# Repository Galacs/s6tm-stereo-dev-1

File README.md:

# S6TM Stereo Dev 1

ESP32S3 based stereo audio developement board with oled display

## IC List

- ESP32-S3FH4R2 (Main MCU)
- x4 LDL212 (LDOs)
- LM74502H (RPP, OCP)
- TPS629330 (5V out of audio SMPS)
- TLV320AIC (CODEC)
- TPA3116D2 (2x 30W audio amplifier)
- TPA3116D2 (OLED display)

## Top preview

## Preview 3d render

## Pictures

## Pin definitions

```c
#define SD_DAT0_PIN 33
#define SD_DAT1_PIN 47
#define SD_DAT2_PIN 37
#define SD_DAT3_PIN 36
#define SD_CLK_PIN 34
#define SD_CMD_PIN 35

#define SW_A_PIN 2
#define BTN_A_PIN 4
#define BTN_B_PIN 3

#define PG_PIN 5
#define VSNS_PIN 6

#define I2C_SDA_PIN 8
#define I2C_SCL_PIN 7

#define ENC_A_PIN 38
#define ENC_B_PIN 39
#define ENC_SW 40

#define FAULTZ_PIN 17
#define MUTE_PIN 21

#define GPIO1_PIN 15
#define RESET_PIN 16
#define BCLK_PIN 10
#define DOUT_PIN 13
#define DIN_PIN 12
#define MCLK_PIN 9
#define WCLK_PIN 11
```

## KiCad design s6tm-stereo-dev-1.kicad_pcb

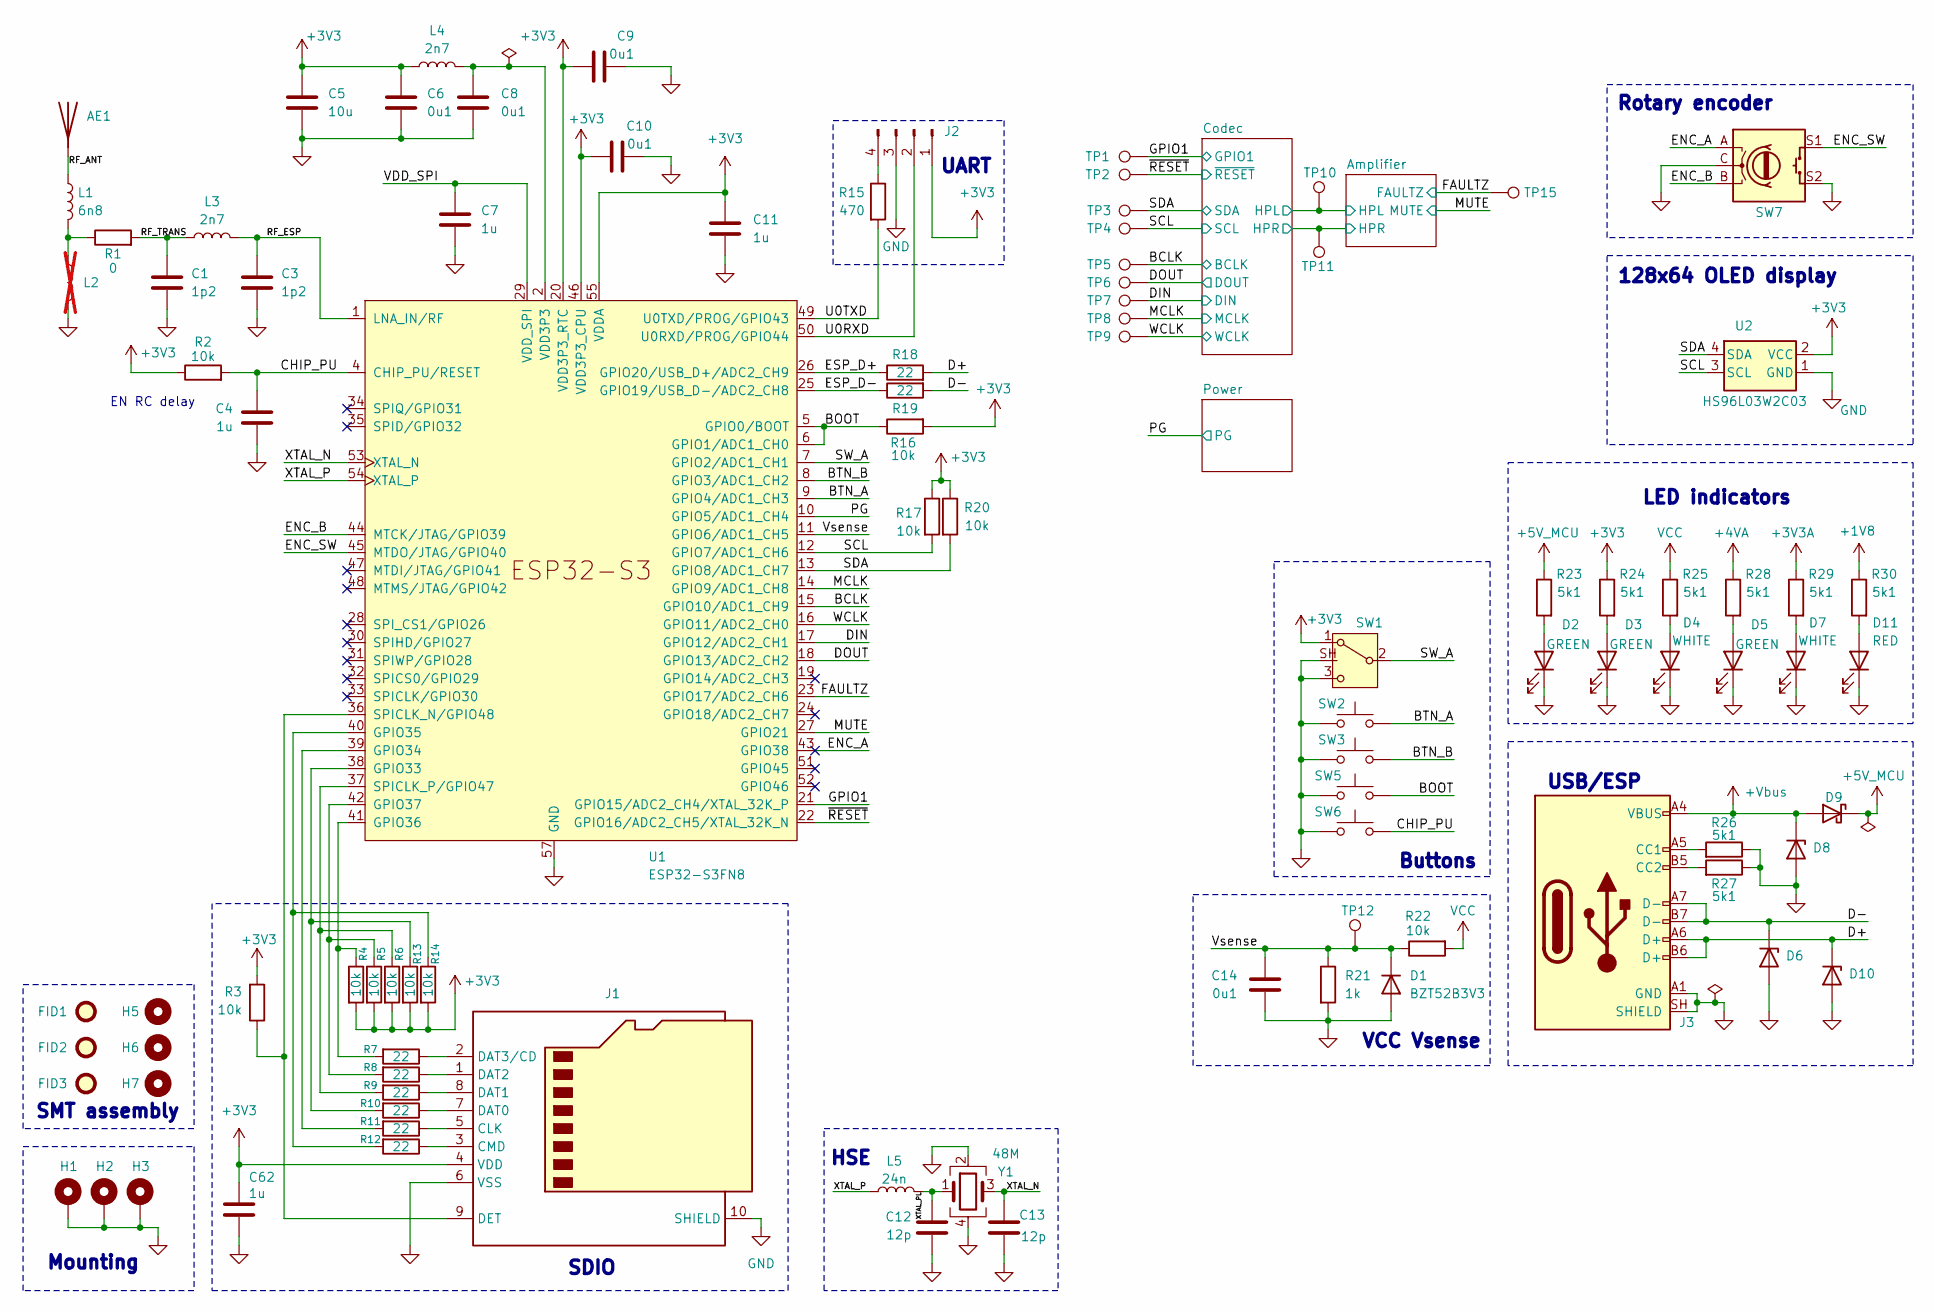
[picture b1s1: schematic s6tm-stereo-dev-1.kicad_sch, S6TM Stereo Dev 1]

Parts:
AE1: Antenna; Johanson_2450AT18x100; Manufacturer Part Number RFANT3216120A5T; JLCPCB Part # C127629
C1, C3: 1p2; C_0402_1005Metric; Manufacturer Part Number GJM1555C1H1R2WB01D; JLCPCB Part # C76899
C4, C7, C11, C62: 1u; C_0402_1005Metric; Manufacturer Part Number CL05A105KA5NQNC; JLCPCB Part # C52923
C5: 10u; C_0402_1005Metric; Manufacturer Part Number CL05A106MQ5NUNC; JLCPCB Part # C15525
C6, C8, C9, C10, C14: 0u1; C_0402_1005Metric; Manufacturer Part Number CL05B104KB54PNC; JLCPCB Part # C307331
C12, C13: 12p; C_0402_1005Metric; Manufacturer Part Number 0402CG120J500NT; JLCPCB Part # C1547
D1: BZT52B3V3; D_SOD-123; Manufacturer Part Number BZT52B3V3; JLCPCB Part # C19077392
D2, D3, D5: GREEN; LED_0805_2012Metric; Manufacturer Part Number KT-0805G; JLCPCB Part # C2297
D4, D7: WHITE; LED_0603_1608Metric; Manufacturer Part Number KT-0603W; JLCPCB Part # C2290
D6, D8, D10: H5VU10U; Diode_DFN1006; Manufacturer Part Number H5VU10U; JLCPCB Part # C22395519
D9: D_Schottky; D_SMA; Manufacturer Part Number SS54; JLCPCB Part # C22452
D11: RED; LED_0805_2012Metric; Manufacturer Part Number NCD0805R1; JLCPCB Part # NCD0805R1
FID1, FID2, FID3: Fiducial; Fiducial_1mm_Mask2mm
H1, H2, H3: MountingHole_Pad; MountingHole_3.2mm_M3_Pad_Via
H5, H6, H7: MountingHole; ToolingHole_1.152mm
J1: Micro_SD_Card_Det1; microSD_Hanbo_TF012; Manufacturer Part Number TF-012; JLCPCB Part # C410350
J2: Conn_01x04_Pin; PinHeader_1x04_P2.54mm_Vertical
J3: USB_C_Receptacle_USB2.0_14P; USB_C_Receptacle_HRO_TYPE-C-31-M-12; Manufacturer Part Number TYPE-C16PIN; JLCPCB Part # C393939
L1: 6n8; L_0402_1005Metric; Manufacturer Part Number LQG15HS6N8J02D; JLCPCB Part # C77110
L2: L; L_0402_1005Metric; not fitted
L3, L4: 2n7; L_0402_1005Metric; Manufacturer Part Number LQG15HS2N7S02D; JLCPCB Part # C77108
L5: 24n; L_0402_1005Metric; Manufacturer Part Number LQW15AN24NG00D; JLCPCB Part # C167472
R1: 0; R_0402_1005Metric; Manufacturer Part Number 0402WGF0000TCE; JLCPCB Part # C17168
R2, R3, R4, R5, R6, R13, R14, R16, R17, R20, R22: 10k; R_0402_1005Metric; Manufacturer Part Number 0402WGF1002TCE; JLCPCB Part # C25744
R7, R8, R9, R10, R11, R12, R18, R19: 22; R_0402_1005Metric; Manufacturer Part Number 0402WGF220JTCE; JLCPCB Part # C25092
R15: 470; R_0402_1005Metric; Manufacturer Part Number 0402WGF4700TCE; JLCPCB Part # C25117
R21: 1k; R_0402_1005Metric; Manufacturer Part Number 0402WGF1001TCE; JLCPCB Part # C11702
R23, R24, R25, R26, R27, R28, R29, R30: 5k1; R_0402_1005Metric; Manufacturer Part Number 0402WGF5101TCE; JLCPCB Part # C25905
SW1: SW_SPDT; SW_SPDT_Shouhan_MSK12C02; Manufacturer Part Number MSK12C02; JLCPCB Part # C431540
SW2, SW3: SW_Push; SW_SPST_Omron_B3F-40xx; Manufacturer Part Number B3F-4055; JLCPCB Part # C84931
SW5, SW6: SW_Push; SW_SPST_TS-1088-xR020; Manufacturer Part Number TS-1088-AR02016; JLCPCB Part # C720477
SW7: RotaryEncoder_Switch; RotaryEncoder_Alps_EC11E-Switch_Vertical_H20mm; Manufacturer Part Number EC11E15244G1; JLCPCB Part # C370970
TP1, TP2, TP12, TP15: TestPoint; TestPoint_Pad_D2.0mm
TP3, TP4, TP5, TP6, TP7, TP8, TP9, TP10, TP11: TestPoint; TestPoint_Keystone_5015_Micro_Mini; Manufacturer Part Number 5015; JLCPCB Part # C2906768
U1: ESP32-S3FN8; QFN-56-1EP_7x7mm_P0.4mm_EP4x4mm_ThermalVias; Manufacturer Part Number ESP32-S3FH4R2; JLCPCB Part # C3013940
U2: HS96L03W2C03
Y1: 48M; Crystal_SMD_2016-4Pin_2.0x1.6mm; Manufacturer Part Number R940000096; JLCPCB Part # C7206306

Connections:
+1V8: R30.1; also elsewhere on the board
+3V3: C5.1, C6.1, C9.1, C10.1, C11.1, C62.1, J1.4 (VDD), J2.1, L4.1, R2.1, R3.2, R4.2, R5.2, R6.2, R13.2, R14.2, R16.2, R17.1, R20.1, R24.1, SW1.1 (A), U1.20 (VDD3P3_RTC), U1.46 (VDD3P3_CPU), U1.55 (VDDA), U1.56 (VDDA), U2.2 (VCC); also elsewhere on the board
+3V3A: R29.1; also elsewhere on the board
+4VA: R28.1; also elsewhere on the board
+5V_MCU: D9.1 (K), R23.1; also elsewhere on the board
+Vbus: D8.1 (K), D9.2 (A), J3.A4 (VBUS), J3.A9 (VBUS), J3.B4 (VBUS), J3.B9 (VBUS)
/Amplifier/HPL: TP10.1 (1_1); also elsewhere on the board
/Amplifier/HPR: TP11.1 (1_1); also elsewhere on the board
/BCLK: TP5.1 (1_1), U1.15 (GPIO10/ADC1_CH9); also elsewhere on the board
/BOOT: R16.1, SW5.2, U1.5 (GPIO0/BOOT), U1.6 (GPIO1/ADC1_CH0)
/BTN_A: SW2.1, U1.9 (GPIO4/ADC1_CH3)
/BTN_B: SW3.1, U1.8 (GPIO3/ADC1_CH2)
/CHIP_PU: C4.1, R2.2, SW6.2, U1.4 (CHIP_PU/RESET)
/D+: D10.1 (K), J3.A6 (D+), J3.B6 (D+), R18.2
/D-: D6.1 (K), J3.A7 (D-), J3.B7 (D-), R19.2
/DIN: TP7.1 (1_1), U1.17 (GPIO12/ADC2_CH1); also elsewhere on the board
/DOUT: TP6.1 (1_1), U1.18 (GPIO13/ADC2_CH2); also elsewhere on the board
/ENC_A: SW7.A, U1.43 (GPIO38)
/ENC_B: SW7.B, U1.44 (MTCK/JTAG/GPIO39)
/ENC_SW: SW7.S1, U1.45 (MTDO/JTAG/GPIO40)
/ESP_D+: R18.1, U1.26 (GPIO20/USB_D+/ADC2_CH9)
/ESP_D-: R19.1, U1.25 (GPIO19/USB_D-/ADC2_CH8)
/FAULTZ: TP15.1 (1_1), U1.23 (GPIO17/ADC2_CH6); also elsewhere on the board
/GPIO1: TP1.1 (1_1), U1.21 (GPIO15/ADC2_CH4/XTAL_32K_P); also elsewhere on the board
/MCLK: TP8.1 (1_1), U1.14 (GPIO9/ADC1_CH8); also elsewhere on the board
/MUTE: U1.27 (GPIO21); also elsewhere on the board
/PG: U1.10 (GPIO5/ADC1_CH4); also elsewhere on the board
/RF_ANT: AE1.1 (A_1), L1.1
/RF_ESP: C3.1, L3.2, U1.1 (LNA_IN/RF)
/RF_TRANS: C1.1, L3.1, R1.2
/SCL: R17.2, TP4.1 (1_1), U1.12 (GPIO7/ADC1_CH6), U2.3 (SCL); also elsewhere on the board
/SDA: R20.2, TP3.1 (1_1), U1.13 (GPIO8/ADC1_CH7), U2.4 (SDA); also elsewhere on the board
/SW_A: SW1.2 (B), U1.7 (GPIO2/ADC1_CH1)
/U0RXD: J2.2, U1.50 (U0RXD/PROG/GPIO44)
/U0TXD: R15.2, U1.49 (U0TXD/PROG/GPIO43)
/VDD_SPI: C7.1, U1.29 (VDD_SPI)
/Vsense: C14.1, D1.1 (K), R21.1, R22.1, TP12.1 (1_1), U1.11 (GPIO6/ADC1_CH5)
/WCLK: TP9.1 (1_1), U1.16 (GPIO11/ADC2_CH0); also elsewhere on the board
/XTAL_N: C13.1, U1.53 (XTAL_N), Y1.3
/XTAL_P: L5.1, U1.54 (XTAL_P)
/XTAL_PL: C12.2, L5.2, Y1.1
/~RESET: TP2.1 (1_1), U1.22 (GPIO16/ADC2_CH5/XTAL_32K_N); also elsewhere on the board
GND: C1.2, C3.2, C4.2, C5.2, C6.2, C7.2, C8.2, C9.2, C10.2, C11.2, C12.1, C13.2, C14.2, C62.2, D1.2 (A), D2.1 (K), D3.1 (K), D4.1 (K), D5.1 (K), D6.2 (A), D7.1 (K), D8.2 (A), D10.2 (A), D11.1 (K), H1.1 (1_1), H2.1 (1_1), H3.1 (1_1), J1.6 (VSS), J1.10 (SHIELD), J2.3, J3.A1 (GND), J3.A12 (GND), J3.B1 (GND), J3.B12 (GND), J3.SH (SHIELD), L2.2, R21.2, R26.1, R27.1, SW1.3 (C), SW1.SH, SW2.2, SW3.2, SW5.1, SW6.1, SW7.C, SW7.S2, U1.57 (GND), U2.1 (GND), Y1.2, Y1.4; also elsewhere on the board
unnamed: D2.2 (A), R23.2
unnamed: D3.2 (A), R24.2
unnamed: D4.2 (A), R25.2
unnamed: D5.2 (A), R28.2
unnamed: D7.2 (A), R29.2
unnamed: D11.2 (A), R30.2
unnamed: J1.5 (CLK), R11.1
unnamed: J1.3 (CMD), R12.1
unnamed: J1.7 (DAT0), R10.1
unnamed: J1.8 (DAT1), R9.1
unnamed: J1.1 (DAT2), R8.1
unnamed: J1.2 (DAT3/CD), R7.1
unnamed: J1.9 (DET), R3.1, U1.36 (SPICLK_N/GPIO48)
unnamed: J2.4, R15.1
unnamed: J3.A5 (CC1), R26.2
unnamed: J3.B5 (CC2), R27.2
unnamed: L1.2, L2.1, R1.1
unnamed: R10.2, R13.1, U1.38 (GPIO33)
unnamed: R11.2, U1.39 (GPIO34)
unnamed: R12.2, R14.1, U1.40 (GPIO35)
unnamed: R4.1, R7.2, U1.41 (GPIO36)
unnamed: R5.1, R8.2, U1.42 (GPIO37)
unnamed: R6.1, R9.2, U1.37 (SPICLK_P/GPIO47)
VCC: R22.2, R25.1; also elsewhere on the board
VDD3P3: C8.1, L4.2, U1.2 (VDD3P3), U1.3 (VDD3P3)

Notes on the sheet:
Mounting
Rotary encoder
HSE
UART
128x64 OLED display
SMT assembly
SDIO
EN RC delay
VCC Vsense
USB/ESP
Buttons
LED indicators

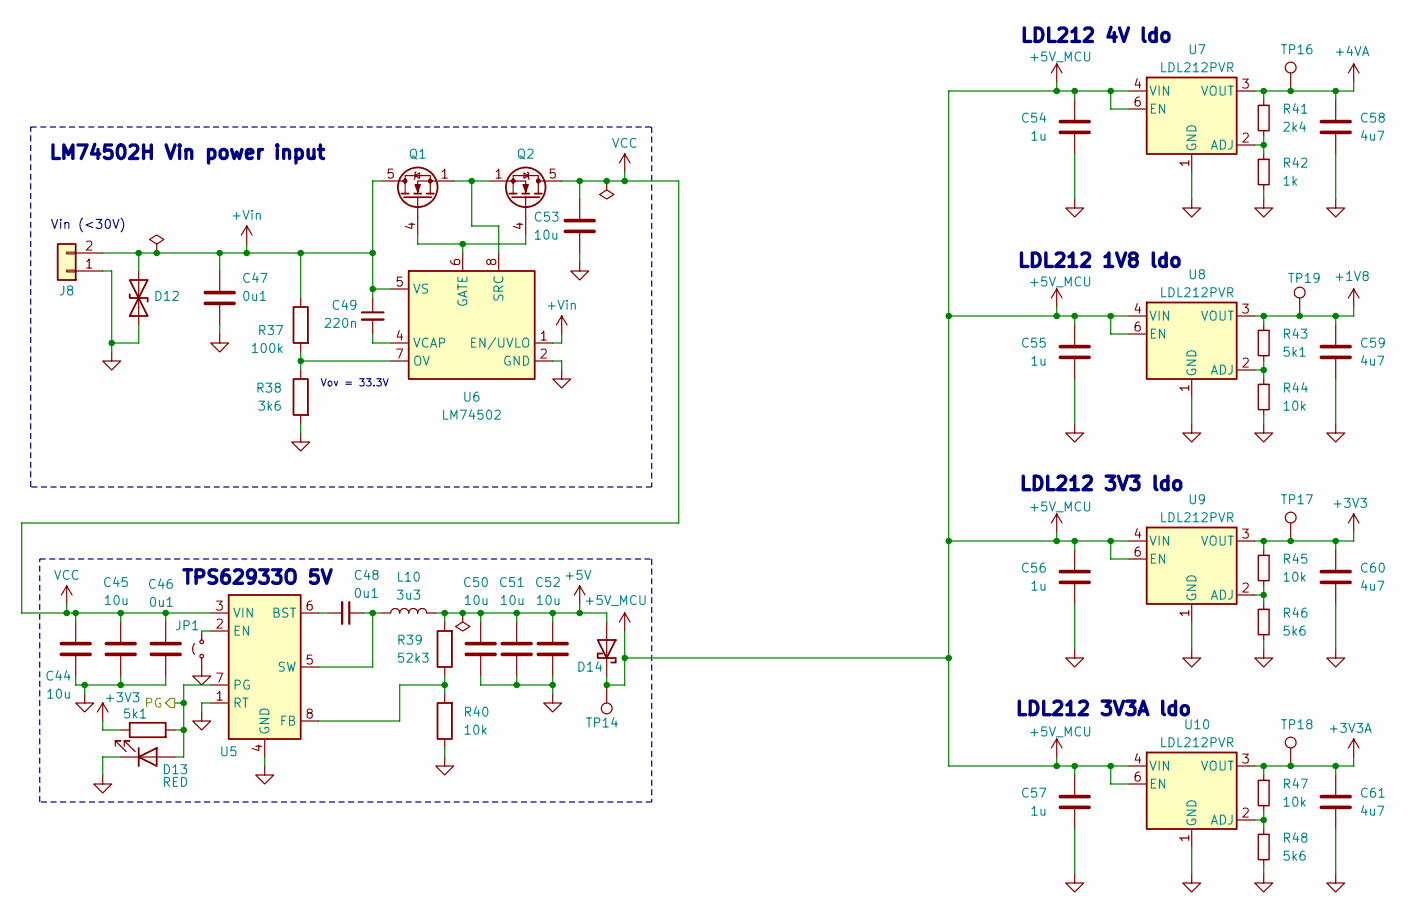
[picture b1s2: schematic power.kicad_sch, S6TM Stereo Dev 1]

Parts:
C44, C45, C50, C51, C52, C53: 10u; C_0805_2012Metric; Manufacturer Part Number GRM21BR61H106KE43L; JLCPCB Part # C440198
C46, C47, C48: 0u1; C_0402_1005Metric; Manufacturer Part Number CL05B104KB54PNC; JLCPCB Part # C307331
C49: 220n; C_0402_1005Metric; Manufacturer Part Number CL05B224KO5NNNC; JLCPCB Part # C16772
C54, C55, C56, C57: 1u; C_0402_1005Metric; Manufacturer Part Number CL05A105KA5NQNC; JLCPCB Part # C52923
C58, C59, C60, C61: 4u7; C_0402_1005Metric; Manufacturer Part Number CL05A475MP5NRNC; JLCPCB Part # C23733
D12: D_TVS; D_SMB; Manufacturer Part Number SMBJ30CA; JLCPCB Part # C2925441
D13: RED; LED_0805_2012Metric; Manufacturer Part Number NCD0805R1; JLCPCB Part # NCD0805R1
D14: D_Schottky; D_SMA; Manufacturer Part Number SS54; JLCPCB Part # C22452
J8: Conn_01x02; TerminalBlock_Phoenix_MKDS-1,5-2-5.08_1x02_P5.08mm_Horizont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
JP1: Jumper_2_Small_Open; PinHeader_1x02_P2.54mm_Vertical
L10: 3u3; L_Sunlord_MWSA0402S; Manufacturer Part Number FXL0420-3R3-M; JLCPCB Part # C167207
Q1, Q2: Q_NMOS; Vishay_PowerPAK_1212-8_Single; Manufacturer Part Number SIS412DN-T1-GE3; JLCPCB Part # C111309
R36, R43: 5k1; R_0402_1005Metric; Manufacturer Part Number 0402WGF5101TCE; JLCPCB Part # C25905
R37: 100k; R_0402_1005Metric; Manufacturer Part Number 0402WGF1003TCE; JLCPCB Part # C25741
R38: 3k6; R_0603_1608Metric; Manufacturer Part Number 0603WAF3601T5E; JLCPCB Part # C22980
R39: 52k3; R_0402_1005Metric; Manufacturer Part Number 0402WGF5232TCE; JLCPCB Part # C26982
R40, R44, R45, R47: 10k; R_0402_1005Metric; Manufacturer Part Number 0402WGF1002TCE; JLCPCB Part # C25744
R41: 2k4; R_0402_1005Metric; Manufacturer Part Number 0402WGF2401TCE; JLCPCB Part # C25882
R42: 1k; R_0402_1005Metric; Manufacturer Part Number 0402WGF1001TCE; JLCPCB Part # C11702
R46, R48: 5k6; R_0402_1005Metric; Manufacturer Part Number 0402WGF5601TCE; JLCPCB Part # C25908
TP14, TP19: TestPoint; TestPoint_Keystone_5015_Micro_Mini; Manufacturer Part Number 5015; JLCPCB Part # C2906768
TP16, TP17, TP18: TestPoint; TestPoint_Pad_D2.0mm
U5: TPS62933O; SOT-583-8; Manufacturer Part Number TPS62933ODRLR; JLCPCB Part # C6290372
U6: LM74502; SOT-23-THIN-8; Manufacturer Part Number LM74502DDFR; JLCPCB Part # C3236215
U7, U8, U9, U10: LDL212PVR; DFN-6-1EP_2x2mm_P0.5mm_ST; Manufacturer Part Number LDL212PVR; JLCPCB Part # C2969922

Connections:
+1V8: C59.1, R43.1, TP19.1 (1_1), U8.3 (VOUT); also elsewhere on the board
+3V3: C60.1, R36.1, R45.1, TP17.1 (1_1), U9.3 (VOUT); also elsewhere on the board
+3V3A: C61.1, R47.1, TP18.1 (1_1), U10.3 (VOUT); also elsewhere on the board
+4VA: C58.1, R41.1, TP16.1 (1_1), U7.3 (VOUT); also elsewhere on the board
+5V: C50.1, C51.1, C52.1, D14.2 (A), L10.2, R39.2
+5V_MCU: C54.1, C55.1, C56.1, C57.1, D14.1 (K), TP14.1 (1_1), U7.4 (VIN), U7.6 (EN), U8.4 (VIN), U8.6 (EN), U9.4 (VIN), U9.6 (EN), U10.4 (VIN), U10.6 (EN); also elsewhere on the board
+Vin: C47.1, C49.1, D12.2 (A2), J8.2, Q1.5 (D), R37.1, U6.1 (EN/UVLO), U6.5 (VS)
/PG: D13.2 (A), R36.2, U5.7 (PG); also elsewhere on the board
GND: C44.2, C45.2, C46.2, C47.2, C50.2, C51.2, C52.2, C53.2, C54.2, C55.2, C56.2, C57.2, C58.2, C59.2, C60.2, C61.2, D12.1 (A1), D13.1 (K), J8.1, JP1.1 (A), R38.2, R40.1, R42.2, R44.2, R46.2, R48.2, U5.1 (RT), U5.4 (GND), U6.2 (GND), U7.1 (GND), U8.1 (GND), U9.1 (GND), U10.1 (GND); also elsewhere on the board
unnamed: JP1.2 (B), U5.2 (EN)
unnamed: Q1.4 (G), Q2.4 (G), U6.6 (GATE)
unnamed: C48.2, U5.6 (BST)
unnamed: R39.1, R40.2, U5.8 (FB)
unnamed: C48.1, L10.1, U5.5 (SW)
unnamed: R37.2, R38.1, U6.7 (OV)
unnamed: Q1.1 (S), Q1.2 (S), Q1.3 (S), Q2.1 (S), Q2.2 (S), Q2.3 (S), U6.8 (SRC)
unnamed: C49.2, U6.4 (VCAP)
unnamed: R41.2, R42.1, U7.2 (ADJ)
unnamed: R43.2, R44.1, U8.2 (ADJ)
unnamed: R45.2, R46.1, U9.2 (ADJ)
unnamed: R47.2, R48.1, U10.2 (ADJ)
VCC: C44.1, C45.1, C46.1, C53.1, Q2.5 (D), U5.3 (VIN); also elsewhere on the board

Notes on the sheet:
LDL212 3V3A ldo
Vov = 33.3V
Vin (<30V)
TPS62933O 5V
LDL212 4V ldo
LDL212 1V8 ldo
LM74502H Vin power input
LDL212 3V3 ldo

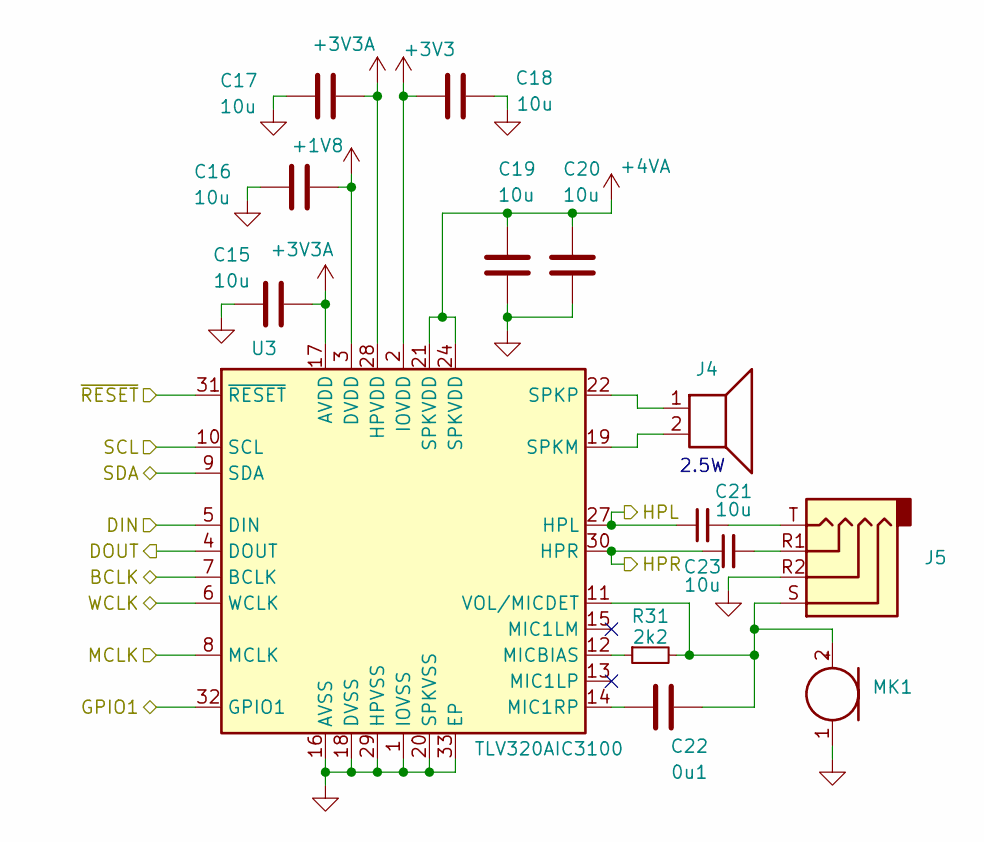
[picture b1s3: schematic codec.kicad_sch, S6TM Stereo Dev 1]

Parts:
C15, C16, C17, C18, C19, C20: 10u; C_0402_1005Metric; Manufacturer Part Number CL05A106MQ5NUNC; JLCPCB Part # C15525
C21, C23: 10u; C_0805_2012Metric; Manufacturer Part Number GRM21BR61H106KE43L; JLCPCB Part # C440198
C22: 0u1; C_0402_1005Metric; Manufacturer Part Number CL05B104KB54PNC; JLCPCB Part # C307331
J4: Conn_01x02; JST_PH_B2B-PH-K_1x02_P2.00mm_Vertical
J5: AudioJack4; Jack_3.5mm_KoreanHropartsElec_PJ-320D-4A_Horizontal; Manufacturer Part Number PJ-320D; JLCPCB Part # C521460
MK1: Microphone; JST_PH_B2B-PH-K_1x02_P2.00mm_Vertical
R31: 2k2; R_0402_1005Metric; Manufacturer Part Number 0402WGF2201TCE; JLCPCB Part # C25879
U3: TLV320AIC3100; VQFN-32-1EP_5x5mm_P0.5mm_EP3.5x3.5mm; Manufacturer Part Number TLV320AIC3100IRHBR; JLCPCB Part # C478458

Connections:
+1V8: C16.2, U3.3 (DVDD); also elsewhere on the board
+3V3: C18.2, U3.2 (IOVDD); also elsewhere on the board
+3V3A: C15.2, C17.2, U3.17 (AVDD), U3.28 (HPVDD); also elsewhere on the board
+4VA: C19.1, C20.1, U3.21 (SPKVDD), U3.24 (SPKVDD); also elsewhere on the board
/Amplifier/HPL: C21.1, U3.27 (HPL); also elsewhere on the board
/Amplifier/HPR: C23.1, U3.30 (HPR); also elsewhere on the board
/BCLK: U3.7 (BCLK); also elsewhere on the board
/DIN: U3.5 (DIN); also elsewhere on the board
/DOUT: U3.4 (DOUT); also elsewhere on the board
/GPIO1: U3.32 (GPIO1); also elsewhere on the board
/MCLK: U3.8 (MCLK); also elsewhere on the board
/SCL: U3.10 (SCL); also elsewhere on the board
/SDA: U3.9 (SDA); also elsewhere on the board
/WCLK: U3.6 (WCLK); also elsewhere on the board
/~RESET: U3.31 (~RESET); also elsewhere on the board
GND: C15.1, C16.1, C17.1, C18.1, C19.2, C20.2, J5.R2, MK1.1 (-), U3.1 (IOVSS), U3.16 (AVSS), U3.18 (DVSS), U3.20 (SPKVSS), U3.25 (SPKVSS), U3.29 (HPVSS), U3.33 (EP); also elsewhere on the board
unnamed: C21.2, J5.T
unnamed: C23.2, J5.R1
unnamed: J4.1, U3.22 (SPKP), U3.26 (SPKP)
unnamed: J4.2, U3.19 (SPKM), U3.23 (SPKM)
unnamed: C22.2, J5.S, MK1.2 (+), R31.2, U3.11 (VOL/MICDET)
unnamed: C22.1, U3.14 (MIC1RP)
unnamed: R31.1, U3.12 (MICBIAS)

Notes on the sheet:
2.5W

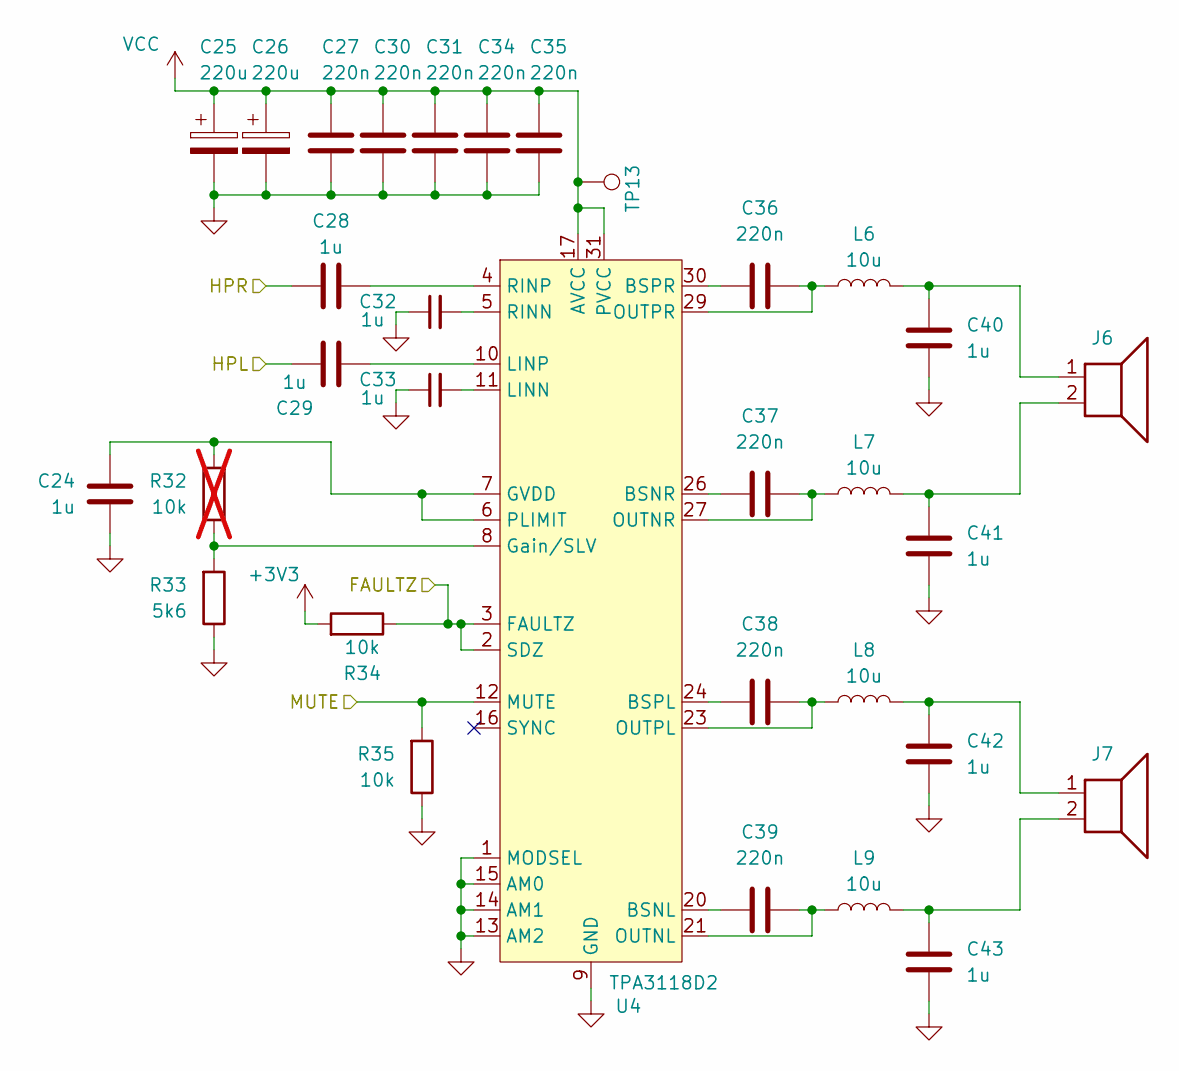
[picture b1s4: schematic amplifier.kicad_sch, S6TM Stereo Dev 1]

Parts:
C24, C28, C29, C32, C33, C40, C41, C42, C43: 1u; C_0402_1005Metric; Manufacturer Part Number CL05A105KA5NQNC; JLCPCB Part # C52923
C25, C26: 220u; CP_Elec_8x10; Manufacturer Part Number UCD1V221MNL1GS; JLCPCB Part # C136294
C27, C30, C31, C34, C35, C36, C37, C38, C39: 220n; C_0402_1005Metric; Manufacturer Part Number CL05B224KO5NNNC; JLCPCB Part # C16772
J6, J7: Conn_01x02; JST_XH_B2B-XH-A_1x02_P2.50mm_Vertical
L6, L7, L8, L9: 10u; L_Vishay_IHLP-4040; Manufacturer Part Number IHLP4040DZER100M01; JLCPCB Part # C845065
R32: 10k; R_0603_1608Metric; not fitted
R33: 5k6; R_0603_1608Metric; Manufacturer Part Number 0603WAF5601T5E; JLCPCB Part # C23189
R34, R35: 10k; R_0402_1005Metric; Manufacturer Part Number 0402WGF1002TCE; JLCPCB Part # C25744
TP13: TestPoint; TestPoint_Keystone_5015_Micro_Mini; Manufacturer Part Number 5015; JLCPCB Part # C2906768
U4: TPA3118D2; HTSSOP-32-1EP_6.1x11mm_P0.65mm_EP5.2x11mm_Mask4.11x4.36mm_T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; Manufacturer Part Number TPA3118D2DAPR; JLCPCB Part # C46497

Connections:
+3V3: R34.2; also elsewhere on the board
/Amplifier/HPL: C29.2; also elsewhere on the board
/Amplifier/HPR: C28.1; also elsewhere on the board
/FAULTZ: R34.1, U4.2 (SDZ), U4.3 (FAULTZ); also elsewhere on the board
/MUTE: R35.2, U4.12 (MUTE); also elsewhere on the board
GND: C24.2, C25.2, C26.2, C27.2, C30.2, C31.2, C32.1, C33.1, C34.2, C35.2, C40.2, C41.2, C42.2, C43.2, R33.1, R35.1, U4.1 (MODSEL), U4.9 (GND), U4.13 (AM2), U4.14 (AM1), U4.15 (AM0), U4.22 (GND), U4.25 (GND), U4.28 (GND), U4.33 (GND); also elsewhere on the board
unnamed: C40.1, J6.1, L6.2
unnamed: C41.1, J6.2, L7.2
unnamed: C42.1, J7.1, L8.2
unnamed: C43.1, J7.2, L9.2
unnamed: C39.1, U4.20 (BSNL)
unnamed: C37.1, U4.26 (BSNR)
unnamed: C38.1, U4.24 (BSPL)
unnamed: C36.1, U4.30 (BSPR)
unnamed: C24.1, R32.2, U4.6 (PLIMIT), U4.7 (GVDD)
unnamed: R32.1, R33.2, U4.8 (Gain/SLV)
unnamed: C33.2, U4.11 (LINN)
unnamed: C29.1, U4.10 (LINP)
unnamed: C39.2, L9.1, U4.21 (OUTNL)
unnamed: C37.2, L7.1, U4.27 (OUTNR)
unnamed: C38.2, L8.1, U4.23 (OUTPL)
unnamed: C36.2, L6.1, U4.29 (OUTPR)
unnamed: C32.2, U4.5 (RINN)
unnamed: C28.2, U4.4 (RINP)
VCC: C25.1, C26.1, C27.1, C30.1, C31.1, C34.1, C35.1, TP13.1 (1_1), U4.17 (AVCC), U4.18 (PVCC), U4.19 (PVCC), U4.31 (PVCC), U4.32 (PVCC); also elsewhere on the board

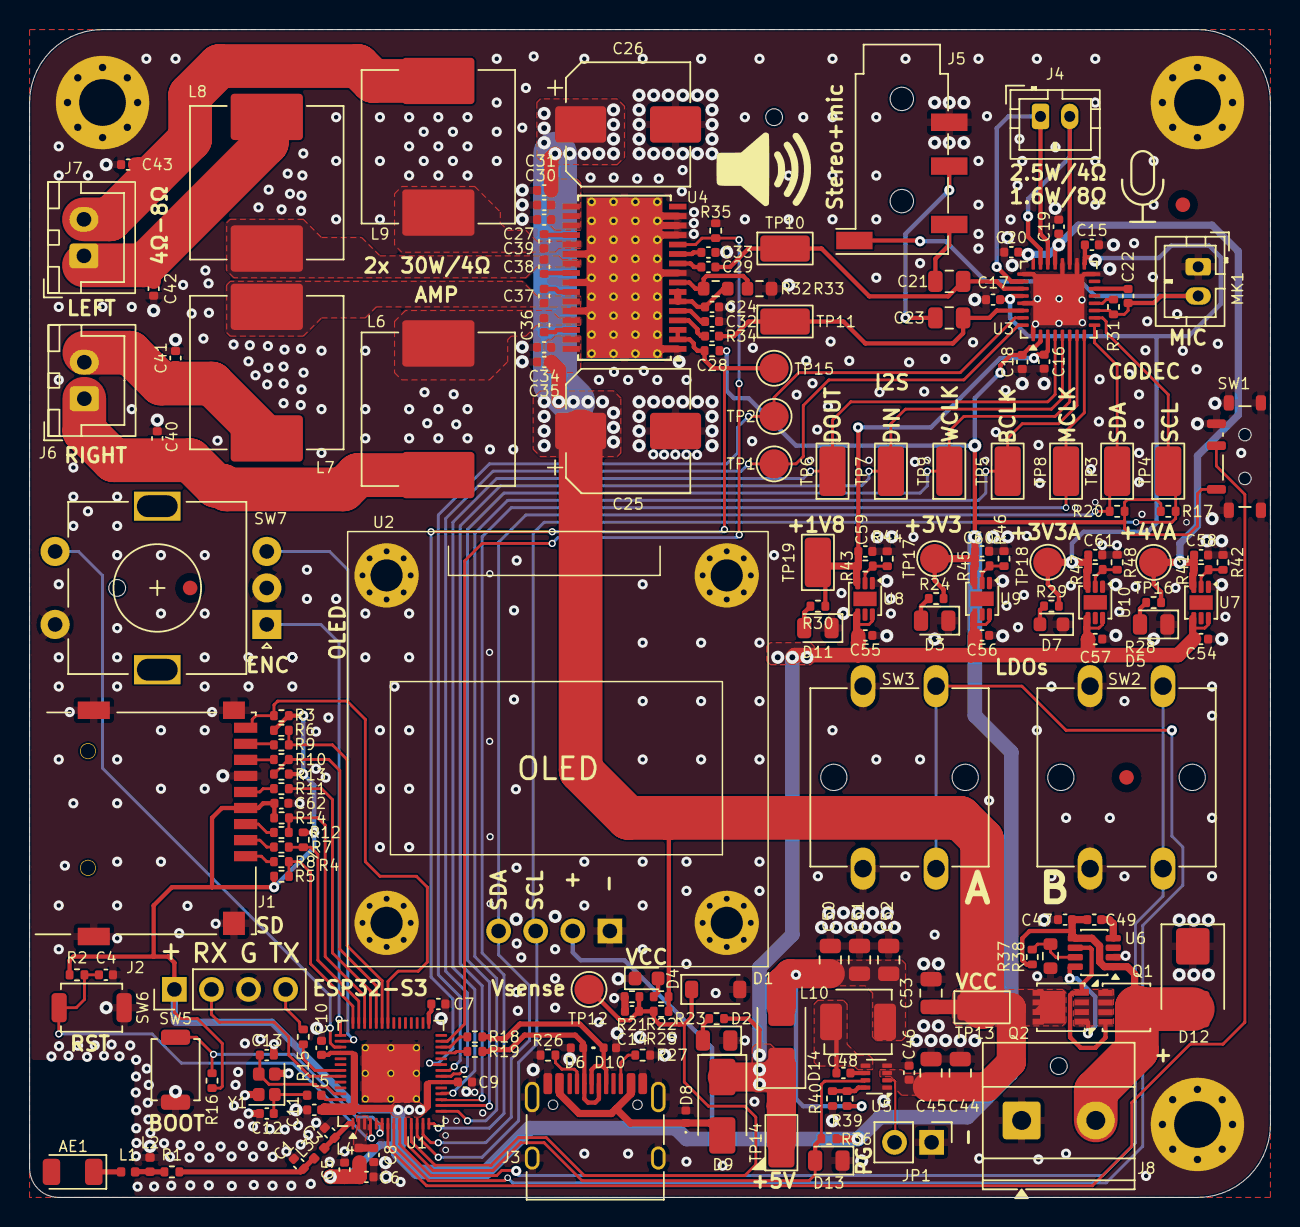
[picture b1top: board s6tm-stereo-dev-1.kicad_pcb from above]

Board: 4 copper layers, 85.0 x 80.0 mm, 191 parts (0 on the bottom side), 107 nets.

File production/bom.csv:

Designator,Footprint,Quantity,Value,LCSC Part #
AE1,Johanson_2450AT18x100,1,Antenna,C127629
"C1, C3",0402,2,1p2,C76899
"C10, C14, C22, C46, C47, C48, C6, C8, C9",0402,9,0u1,C307331
"C11, C24, C28, C29, C32, C33, C4, C40, C41, C42, C43, C54, C55, C56, C57, C62, C7",0402,17,1u,C52923
"C12, C13",0402,2,12p,C1547
"C15, C16, C17, C18, C19, C20, C5",0402,7,10u,C15525
"C21, C23, C44, C45, C50, C51, C52, C53",0805,8,10u,C440198
"C25, C26",CP_Elec_8x10,2,220u,C136294
"C27, C30, C31, C34, C35, C36, C37, C38, C39, C49",0402,10,220n,C16772
"C58, C59, C60, C61",0402,4,4u7,C23733
D1,D_SOD-123,1,BZT52B3V3,C19077392
"D10, D6, D8",Diode_DFN1006,3,H5VU10U,C22395519
"D11, D13",0805,2,RED,NCD0805R1
D12,D_SMB,1,D_TVS,C2925441
"D14, D9",D_SMA,2,D_Schottky,C22452
"D2, D3, D5",0805,3,GREEN,C2297
"D4, D7",0603,2,WHITE,C2290
J1,microSD_Hanbo_TF012,1,Micro_SD_Card_Det1,C410350
J3,USB_C_Receptacle_HRO_TYPE-C-31-M-12,1,USB_C_Receptacle_USB2.0_14P,C393939
J4,JST_PH_B2B-PH-K_1x02_P2.00mm_Vertical,1,Conn_01x02,
J5,Jack_3.5mm_KoreanHropartsElec_PJ-320D-4A_Horizontal,1,AudioJack4,C521460
"J6, J7",JST_XH_B2B-XH-A_1x02_P2.50mm_Vertical,2,Conn_01x02,
L1,0402,1,6n8,C77110
L10,L_Sunlord_MWSA0402S,1,3u3,C167207
"L3, L4",0402,2,2n7,C77108
L5,0402,1,24n,C167472
"L6, L7, L8, L9",L_Vishay_IHLP-4040,4,10u,C845065
MK1,JST_PH_B2B-PH-K_1x02_P2.00mm_Vertical,1,Microphone,
"Q1, Q2",Vishay_PowerPAK_1212-8_Single,2,Q_NMOS,C111309
R1,0402,1,0,C17168
"R10, R11, R12, R18, R19, R7, R8, R9",0402,8,22,C25092
"R13, R14, R16, R17, R2, R20, R22, R3, R34, R35, R4, R40, R44, R45, R47, R5, R6",0402,17,10k,C25744
R15,0402,1,470,C25117
"R21, R42",0402,2,1k,C11702
"R23, R24, R25, R26, R27, R28, R29, R30, R36, R43",0402,10,5k1,C25905
R31,0402,1,2k2,C25879
R33,0603,1,5k6,C23189
R37,0402,1,100k,C25741
R38,0603,1,3k6,C22980
R39,0402,1,52k3,C26982
R41,0402,1,2k4,C25882
"R46, R48",0402,2,5k6,C25908
SW1,SW_SPDT_Shouhan_MSK12C02,1,SW_SPDT,C431540
"SW2, SW3",SW_SPST_Omron_B3F-40xx,2,SW_Push,C84931
"SW5, SW6",SW_SPST_TS-1088-xR020,2,SW_Push,C720477
SW7,RotaryEncoder_Alps_EC11E-Switch_Vertical_H20mm,1,RotaryEncoder_Switch,C370970
"TP10, TP11, TP13, TP14, TP19, TP3, TP4, TP5, TP6, TP7, TP8, TP9",TestPoint_Keystone_5015_Micro_Mini,12,TestPoint,C2906768
U1,QFN-56-1EP_7x7mm_P0.4mm_EP4x4mm_ThermalVias,1,ESP32-S3FN8,C3013940
"U10, U7, U8, U9",DFN-6-1EP_2x2mm_P0.5mm_ST,4,LDL212PVR,C2969922
U3,VQFN-32-1EP_5x5mm_P0.5mm_EP3.5x3.5mm,1,TLV320AIC3100,C478458
U4,HTSSOP-32-1EP_6.1x11mm_P0.65mm_EP5.2x11mm_Mask4.11x4.36mm_ThermalVias,1,TPA3118D2,C46497
U5,SOT-583-8,1,TPS62933O,C6290372
U6,SOT-23-THIN-8,1,LM74502,C3236215
Y1,Crystal_SMD_2016-4Pin_2.0x1.6mm,1,48M,C7206306

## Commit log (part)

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2026-04-13 schem: import ESP32-S3 mcu
2026-04-13 schem: import HSE oscilator
2026-04-13 schem: import USB-C connector
2026-04-13 schem: import LDL212 3V3 ldo
2026-04-13 schem: add TLV320AIC3100 audio codec and switch to adjustable ldo
2026-04-13 schem: add LDL212 1V8 ldo
2026-04-13 schem: add analog 3v3 ldo
2026-04-13 schem: add speaker 4v ldo (le dernier, je le jure)
2026-04-13 schem: add codec power section
2026-04-13 schem: remove "extra" 0u1 capacitors from codec
2026-04-13 schem: add codec surrounding circuitery
2026-04-13 schem: add hierarchical line output labels to codec
2026-04-13 schem: add TPA3118D2 amplifier with power section
2026-04-13 schem: add TPA3118 config components
2026-04-14 schem: finish tpa3118 amplifier page
2026-04-14 schem: connect codec to amplifier
2026-04-14 schem: add buttons
2026-04-14 schem: add TPS62933O 5V OOA buck converter
2026-04-14 schem: add power page and LM74502H Vin power input RPP
2026-04-14 schem: add buck converter PG led
2026-04-14 schem: add led pwr status
2026-04-14 schem: change red led to lower vf
2026-04-14 schem: add power led indicators for all voltage rails
2026-04-14 schem: add PG gpio to buck converter
2026-04-14 schem: add OLED display
2026-04-14 schem: add rotary encoder
2026-04-14 schem: add vcc vsense
2026-04-14 schem: add buck converter disable jumper
2026-04-14 schem: connect pheripherals to mcu gpios
2026-04-14 schem: add sd card slot
2026-04-14 schem: add no connects
2026-04-14 schem: add test points
2026-04-14 schem: add net classes
2026-04-14 schem: add missing footprints
2026-04-14 schem: add ordering info to BOM
2026-04-14 schem: run and fix ERC
2026-04-14 schem: add title
2026-04-14 schem: reannotate
2026-04-14 pcb: import 4 layers jlc stackup and constraints
2026-04-14 pcb: import from schem
2026-04-14 pcb: add missing 3d models
2026-04-14 schem: remove BTN_C
2026-04-14 schem: update esp32s3 footprint
2026-04-14 pcb: initial layout
2026-04-14 schem: add M3 mounting holes
2026-04-14 schem/pcb: add smt fiducials and tooling holes
2026-04-14 schem/pcb: remove extra mounting hole
2026-04-14 pcb: add smps routing
2026-04-14 schem: switch load switch to always on
2026-04-14 pcb: add LM74502H layout
2026-04-14 pcb: add usb layout
2026-04-14 pcb: add LDOs layout
2026-04-15 pcb: rpp and smps layout refinement
2026-04-15 pcb: add audio layout
2026-04-15 pcb: refine amplifier layout
2026-04-15 pcb: refine codec layout
2026-04-15 pcb: add fiducials, tooling holes
2026-04-15 pcb: refine sd layout
2026-04-15 pcb: add board outline
2026-04-15 pcb: add gnd planes
2026-04-15 pcb: add gnd vias
2026-04-15 pcb: add grid/place origin
2026-04-15 pcb: add rf routing
2026-04-15 pcb: add HSE xtal routing
2026-04-15 pcb: add uart routing
2026-04-15 pcb: add sd card routing
2026-04-15 pcb: add LDOs routing
2026-04-15 pcb: add codec routing
2026-04-15 pcb: add amplifier routing
2026-04-15 pcb: add rpp routing
2026-04-15 pcb: add vcc vsense routing
2026-04-15 pcb: add +5V smps routing
2026-04-15 pcb: add VCC power routing
2026-04-15 pcb: add +5V_MCU pwr routing
2026-04-15 pcb: add +3V3 pwr routing
2026-04-15 pcb: add bTN_AB routing
2026-04-15 pcb: add Vsense and PG routing
2026-04-15 pcb: add SW_A routing
2026-04-15 pcb: add I2C routing
2026-04-15 pcb: add codec i2s and gpios routing
2026-04-15 pcb: clean codec traces appearance
2026-04-15 schem: add FAULTZ test point
2026-04-15 pcb: add amplifier gpios routing
2026-04-15 pcb: add BOOT and RST btns routing
2026-04-15 pcb: add encoder routing
2026-04-15 pcb: add codec pwr routing
2026-04-15 pcb: add missing 3v3 routing
2026-04-15 pcb: add stitching vias
2026-04-15 pcb: run and fix DRC
2026-04-15 pcb: remove unused internal pads
2026-04-15 pcb(silk): clean up reference designators
2026-04-15 pcb(silk): add user txt
2026-04-15 pcb: add title
2026-04-15 schem: update headphone jack PN
2026-04-15 generate production files
